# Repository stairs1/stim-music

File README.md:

# StimMusic - Music + GVS

Experience music and vestibular stimulation in sync. Artists can write music with vestibular stimulation channel using a Digital Audio Workstation (DAW) plugin Virtual Studio Technology (VST). A 4-electrode GVS setup allows for stimulation of yaw, pitch, and roll vestibular experience, at various intensities, in sync with music.

## Safety

Nominal: 0 - 4mA @ 9V
Max: 4mA @ 9V

Proper system should have current limiter! Better, multiple redundant current limiter! Don't connect to mains, use a battery!

## Install + Setup

Ubuntu 20 or Mac

Run ESP32s with GVS firmware and hardware setup, GVS to VST Python backend at VST_to_GVS_server_bridge_python, open VST in new track in DAW. Run the steps below to setup each component.

### Backend
1. Setup and activate virtual environment
2. Setup Youtube-dlc globally:
```
sudo wget https://github.com/blackjack4494/yt-dlc/releases/latest/download/youtube-dlc -O /usr/local/bin/youtube-dlc
sudo chmod a+rx /usr/local/bin/youtube-dlc
```
3. Install requirements:
`pip3 install -r requirements.txt`

### Firmware

1. Install Visual Studio Code. `sudo snap install code --classic`
2. Setup Platform IO in visual studio code.
3. Open ./firmware in PlatformIO
4. Flash onto ESP32s with GVS hardware connected.

### VST

1. Install Reaper of Ableton (DAW)
2. Connect MIDI keyboard to DAW
3. Build VST for your system.
4. (LINUX) - see below
5. Install VST in DAW
6. Run VST on track Midi keyboard input

##### Linux setup:

1. Install linux low latency kernel
2. Install JACK: `sudo apt-get install jackd2 qjackctl`
3. Configure JACK to use low latency - https://jackaudio.org/faq/linux_rt_config.html
4. Install m2jmidid `sudo apt-get install a2jmidid`
5. In `qjackctl`, Go to "Setup" -> Set Midi Driver to "seq" -> "Options (tab)" -> "Startup after execute" line: `pacmd set-default-sink jack_out; a2jmidid -e &`
6. Check qjackctl "Connections" -> Midi and ensure Midi keyboard is there.
7. Start JACK -> qjackctl -> Start
8. Set Reaper to use JACK as Audio Device ("Ctrl-P" -> Audio Device -> Set as JACK)
9. Add midi keyboard in reaper.
10. Run the GVS to VST backend server

## Electrode Placement

2 seperate current pathways, so that current doesn't go across the forehead.
   - "Because SDAS and ODAS are applied using two current stimulators (A+/- and B+/-), a part of current emitted from anode A+ may be received by cathode B- when ground-sharing circuits are used. Then, current might not flow as we intended. Therefore, we used isolated current stimulators that were driven by a different battery." 

Each electrode must be able to be cathod or anode.

1. Left mastoid.
2. Right mastoid
3. Left temple
4. Right temple

Ensure there is no current flow from 3 to 4!

## Electrical

3 isolated bipolar circuits, in order to show ensure current flows as expected.

1. Mastoid-mastoid
2. Left mastoid - left temple
3. Right mastoid - right temple

## Subjective Experience 

Yaw, pitch, roll are the primary colors of the vestibular system.

How can we make it feel like we're flying up? Or dropping into the ground? Or accelerating forward so we are pushed back into our chair?

Left roll - 1 cathode, 2 anode 
Right roll - 1 anode, 2 cathod

Front pitch - 1 anode, 3 cathode, 2 anode, 4 cathode
Back pitch - 1 cathod, 3 anode, 2 cathode, 3 anode

Left yaw - 1 cathode, 2 anode, 3 anode, 4 cathode
Right yaw - 1 anode, 2 cathode, 3 cathode, 4 anode

## References

GVS Electrode placement pathways and associated subjective experience: https://www.ncbi.nlm.nih.gov/pmc/articles/PMC4426693/

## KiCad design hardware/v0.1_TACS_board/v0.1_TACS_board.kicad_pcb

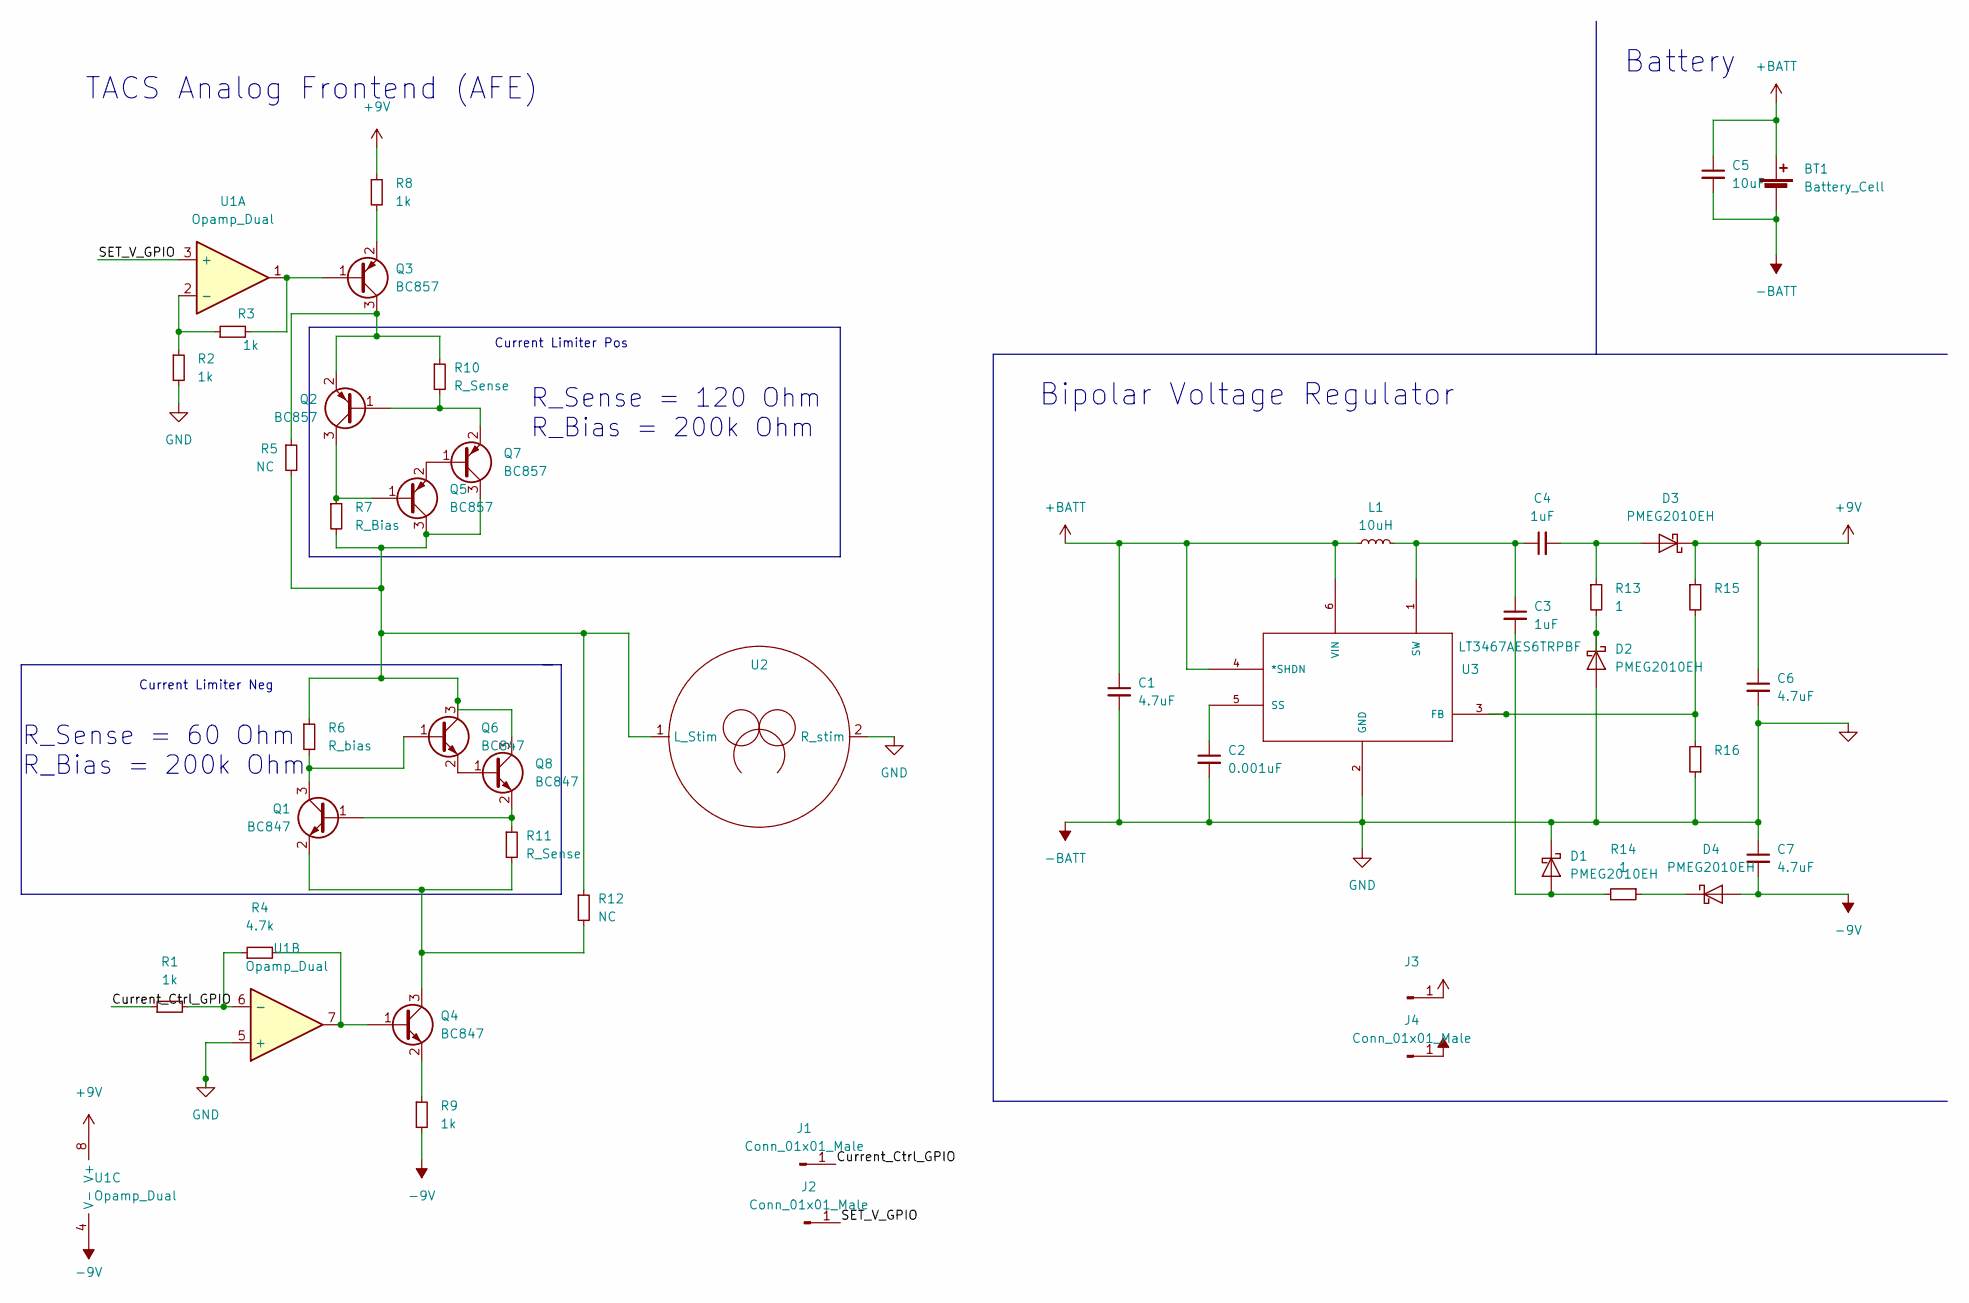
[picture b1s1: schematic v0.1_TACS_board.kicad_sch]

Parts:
BT1: Battery_Cell; BatterySolderOn
C1, C6, C7: 4.7uF; C_0402_1005Metric
C2: 0.001uF; C_0402_1005Metric
C3, C4: 1uF; C_0402_1005Metric
C5: 10uF; C_0603_1608Metric
D1, D2, D3, D4: PMEG2010EH; D_SOD-123F
J1, J2, J4: Conn_01x01_Male; TestPoint_Pad_D2.0mm
J3: (no value)
L1: 10uH; L_0805_2012Metric
Q1, Q4, Q6, Q8: BC847; SOT-23
Q2, Q3, Q5, Q7: BC857; SOT-23
R1, R2, R3, R8, R9: 1k; R_0402_1005Metric
R4: 4.7k; R_0402_1005Metric
R5, R12: NC; R_0805_2012Metric
R6: R_bias; R_0402_1005Metric
R7: R_Bias; R_0402_1005Metric
R10, R11: R_Sense; R_0402_1005Metric
R13, R14: 1; R_0402_1005Metric
R15, R16: (no value)
U1: Opamp_Dual; TSSOP-8_4.4x3mm_P0.65mm
U2: Electrode_Solder_Pads
U3: LT3467AES6TRPBF; SOT-23-6; MANUFACTURER_PART_NUMBER lt3467aes6#trpbf

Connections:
+BATT: BT1.1 (+), C1.1, C5.1, L1.1, U3.4 (*SHDN), U3.6 (VIN)
/Current_Ctrl_GPIO: J1.1, R1.1
/SET_V_GPIO: J2.1, U1.3 (+)
unnamed: C2.1, U3.5 (SS)
unnamed: C3.1, C4.1, L1.2, U3.1 (SW)
unnamed: C3.2, D1.2 (A), R14.2
unnamed: C4.2, D3.2 (A), R13.1
unnamed: D2.1 (K), R13.2
unnamed: D4.1 (K), R14.1
unnamed: Q1.1 (B), Q8.2 (E), R11.1
unnamed: Q1.2 (E), Q4.3 (C), R11.2, R12.2
unnamed: Q1.3 (C), Q6.1 (B), R6.2
unnamed: Q2.1 (B), Q7.2 (E), R10.2
unnamed: Q2.2 (E), Q3.3 (C), R5.1, R10.1
unnamed: Q2.3 (C), Q5.1 (B), R7.1
unnamed: Q3.1 (B), R3.2, U1.1
unnamed: Q3.2 (E), R8.2
unnamed: Q4.1 (B), R4.2, U1.7
unnamed: Q4.2 (E), R9.1
unnamed: Q5.2 (E), Q7.1 (B)
unnamed: Q5.3 (C), Q6.3 (C), Q7.3 (C), Q8.3 (C), R5.2, R6.1, R7.2, R12.1, U2.1 (L_Stim)
unnamed: Q6.2 (E), Q8.1 (B)
unnamed: R1.2, R4.1, U1.6 (-)
unnamed: R2.1, R3.1, U1.2 (-)
unnamed: R15.2, R16.2, U3.3 (FB)

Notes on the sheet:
TACS Analog Frontend (AFE)
Current Limiter Neg
R_Sense = 60 Ohm R_Bias = 200k Ohm
Battery
Bipolar Voltage Regulator
Current Limiter Pos
R_Sense = 120 Ohm R_Bias = 200k Ohm

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
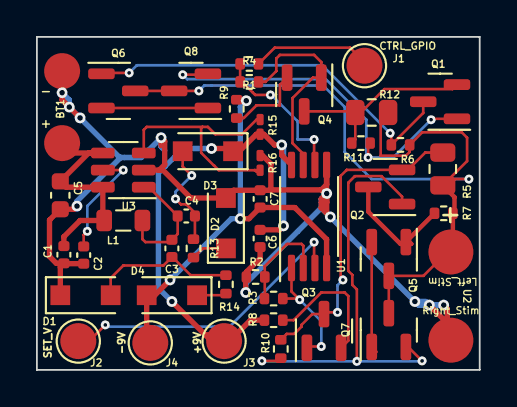
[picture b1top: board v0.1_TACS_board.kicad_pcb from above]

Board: 2 copper layers, 24.6 x 18.5 mm, 44 parts (0 on the bottom side), 28 nets.

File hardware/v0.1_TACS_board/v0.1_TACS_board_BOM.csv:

"Id";"Designator";"Package";"Quantity";"Designation";"Supplier and ref";
1;"R12,R5";"R_0805_2012Metric";2;"NC";;;
2;"J4,J3,J2,J1";"TestPoint_Pad_D2.0mm";4;"Conn_01x01_Male";;;
3;"R7";"R_0402_1005Metric";1;"R_Bias";;;
4;"R3,R2,R1,R8,R9";"R_0402_1005Metric";5;"1k";;;
5;"R10,R11";"R_0402_1005Metric";2;"R_Sense";;;
6;"D3,D1,D4,D2";"D_SOD-123F";4;"PMEG2010EH";;;
7;"Q7,Q2,Q3,Q5";"SOT-23";4;"BC857";;;
8;"L1";"L_0805_2012Metric";1;"10uH";;;
9;"C6,C1,C7";"C_0402_1005Metric";3;"4.7uF";;;
10;"C3,C4";"C_0402_1005Metric";2;"1uF";;;
11;"Q8,Q1,Q6,Q4";"SOT-23";4;"BC847";;;
12;"C2";"C_0402_1005Metric";1;"0.001uF";;;
13;"BT1";"BatterySolderOn";1;"Battery_Cell";;;
14;"R16";"R_0402_1005Metric";1;"?????????";;;
15;"R14,R13";"R_0402_1005Metric";2;"1";;;
16;"U1";"TSSOP-8_4.4x3mm_P0.65mm";1;"Opamp_Dual";;;
17;"C5";"C_0603_1608Metric";1;"10uF";;;
18;"R15";"R_0402_1005Metric";1;"???????";;;
19;"U2";"Electrode_Solder_Pads";1;"Electrodes";;;
20;"R4";"R_0402_1005Metric";1;"4.7k";;;
21;"U3";"SOT-23-6";1;"LT3467AES6TRPBF";;;
22;"R6";"R_0402_1005Metric";1;"R_bias";;;

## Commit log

2022-02-20 Add all socket programs
2022-02-20 SERVER WORKS
2022-02-20 Add firstVST mvp
2022-03-08 ESP32 GATT server for stim control
2022-03-08 Python BLE client
2022-03-08 Add all VST, TCP stuff
2022-03-08 add README
2022-03-08 Add midi number and velocity sending VST code
2022-03-08 move MacVST
2022-03-08 Add linux makefile for VST
2022-03-08 add README instructions, rearrange code
2022-03-08 Add graceful failure server
2022-03-08 add Linux VST (seperate commits because git though new VST was a rename
2022-03-08 laptop-keyboard stim, also DAC control for AC
2022-03-08 Add licence
2022-03-12 dac 8-bit output calculator
2022-03-12 update gitignore
2022-03-12 firmware - AC stim with BLE-DAC Buffer
2022-03-12 backend playing audio, generating stim track from audio, sending stream of stim chunks to stim client while music is playing
2022-03-13 move bluetooth client to a seperate Process so audio playback and BT sending packets can happen at same time
2022-03-13 new chunk based, latency controlled system fully working end to end
2022-03-13 music++ feels good! also add play from youtube from url
2022-03-27 finish schematic of AFE, bipolar regulator, battery supply board, start layout
2022-03-31 finish board TACS board, generate production files, order on jlcpcb
2022-04-17 SPICE models for frontend
2022-04-17 sans-limiter 12V kicad schematic
2022-04-22 SPICE for +- 2V, max 4k head
2022-04-22 dac pin values for wearable test
2022-04-23 add audio bluetooth delay space bar tapping functions, keyboard callback changer, ble client cleanup
2022-04-24 make stim generation function modular
2022-04-24 stim delay estimation
2022-04-24 stim+audio phase alignment now works - make stim track offset work with positive or negative phase shift
2022-05-04 improved microcontroller buffering
2022-05-07 add UI, audio-stim calibration, improve buffering
2022-05-07 Update LICENSE
2022-05-07 stim track designer
